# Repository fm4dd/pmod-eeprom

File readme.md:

## PMOD-EEPROM

### Description

This I2C PMOD provides a 1 Mbit serial EEPROM, using the M24M01 circuit by STMicroelectronics. DIP switches enable I2C pull-up resistors if needed, and change the EEPROM's I2C device address. Up to four modules can be chained for a total capacity of 4 Mbit (512 KBytes). Three Testpoints can be fitted for I2C bus troubleshooting. The PMOD has designs for Type-6 (I2C single row), and for the new Type-6A (I2C extended double row). The picture shows the Type-6A variant (engineering sample).

http://fpga.fm4dd.com/

### Schematic
This is the schema for the PMOD I2C Type-6 (single row) connector variant:

The current EEPROM desin is pulling the "write-protect" pin high for "read-write" operation. A design update may implement a solder pad for setting the EEPROM 'read-only' after programming.

### Hardware Release

|Type     | Version | Gerber | Schema |
|---------|---------|--------|--------|
|Type-6   |1.1      |[EEPROM PMOD Type-6 Gerber V1.1](release/t6-v11/20210917-eeprom-t6-gerber-v11.zip) | [20210917-eeprom-t6-schema-v11.pdf](release/t6-v11/20210917-eeprom-t6-schema-v11.pdf)
|Type-6A  |1.1      |[EEPROM PMOD Type-6A Gerber V1.1](release/t6a-v11/20210814-eeprom-t6a-gerber-v11.zip) | [20210814-eeprom-t6a-schema-v11.pdff](release/t6a-v11/20210814-eeprom-t6a-schema-v11.pdf)

#### Rasperry Pi I2C Discovery

Ensure the I2C bus is enabled, and install prerequisite I2C tools:
```
# sudo apt-get install git i2c-tools
# raspi-config  2 Interface Options  enable I2C
```

Check the IO expander circuit is visible on the I2C bus under address 0x50..0x56, depending on the address set through the DIP switch. Below example address 0x50/51 is set with SW1-1 = off and SW1-2 = off.
```
pi@pi-ms05:~ $ i2cdetect -y 1
     0  1  2  3  4  5  6  7  8  9  a  b  c  d  e  f
00:          -- -- -- -- -- -- -- -- -- -- -- -- --
10: -- -- -- -- -- -- -- -- -- -- -- -- -- -- -- --
20: -- -- -- -- -- -- -- -- -- -- -- -- -- -- -- --
30: -- -- -- -- -- -- -- -- -- -- -- -- -- -- -- --
40: -- -- -- -- -- -- -- -- -- -- -- -- -- -- -- --
50: 50 51 -- -- -- -- -- -- -- -- -- -- -- -- -- --
60: -- -- -- -- -- -- -- -- -- -- -- -- -- -- -- --
70: -- -- -- -- -- -- -- --
```

### Example code

pmod-eeprom code examples for Arduino boards are available in the [example folder](examples/)

On the Raspberry Pi, the PMOD can be easily programmed with the eeprom utility program 'eepflash.sh'. This program writes a manually created byte file (.eep) as content into the I2C eeprom. It can be found as part of the Raspberry Pi foundation 'hats' repository:
```
pi@pi-ms05:~ $ git clone https://github.com/raspberrypi/hats.git
Cloning into 'hats'...
remote: Enumerating objects: 565, done.
remote: Counting objects: 100% (95/95), done.
remote: Compressing objects: 100% (61/61), done.
remote: Total 565 (delta 59), reused 46 (delta 34), pack-reused 470
Receiving objects: 100% (565/565), 306.34 KiB | 936.00 KiB/s, done.
Resolving deltas: 100% (325/325), done.
```

Compile the tools located in the eepromutils subdirectory:
```
pi@pi-ms05:~ $ cd hats/eepromutils/
pi@pi-ms05:~/hats/eepromutils $ make clean; make
rm -f eepmake eepdump
cc -Wall -Wextra eepmake.c -o eepmake
cc -Wall -Wextra eepdump.c -o eepdump
```
Check the tools:
```
pi@pi-ms05:~/hats/eepromutils $ ls -l
total 84
-rwxr-xr-x 1 pi pi 12820 Aug 28 22:38 eepdump
-rw-r--r-- 1 pi pi  8112 Aug 28 22:37 eepdump.c
-rwxr-xr-x 1 pi pi  3906 Aug 28 22:37 eepflash.sh
-rwxr-xr-x 1 pi pi 22232 Aug 28 22:38 eepmake
-rw-r--r-- 1 pi pi 15144 Aug 28 22:37 eepmake.c
-rwxr-xr-x 1 pi pi  3122 Aug 28 22:37 eeprom_settings.txt
-rw-r--r-- 1 pi pi  2395 Aug 28 22:37 eeptypes.h
-rw-r--r-- 1 pi pi   677 Aug 28 22:37 Makefile
-rw-r--r-- 1 pi pi  1836 Aug 28 22:37 README.md
```

Example upload of an .eep file:
```
pi@pi-ms05:~/hats/eepromutils $ sudo ./eepflash.sh -w -f=rpi2pmod.eep -t=24c32 -d=1 -a=50
This will attempt to talk to an eeprom at i2c address 0x50 on bus 1. Make sure there is an eeprom at this address.
This script comes with ABSOLUTELY no warranty. Continue only if you know what you are doing.
Do you wish to continue? (yes/no): yes
Writing...
0+1 records in
0+1 records out
113 bytes copied, 0.728222 s, 0.2 kB/s
Closing EEPROM Device.
Done.
```

PMOD-EEPROM on a PMOD2RPI interface board, running code from the XIAO Cortex M0+ MCU.

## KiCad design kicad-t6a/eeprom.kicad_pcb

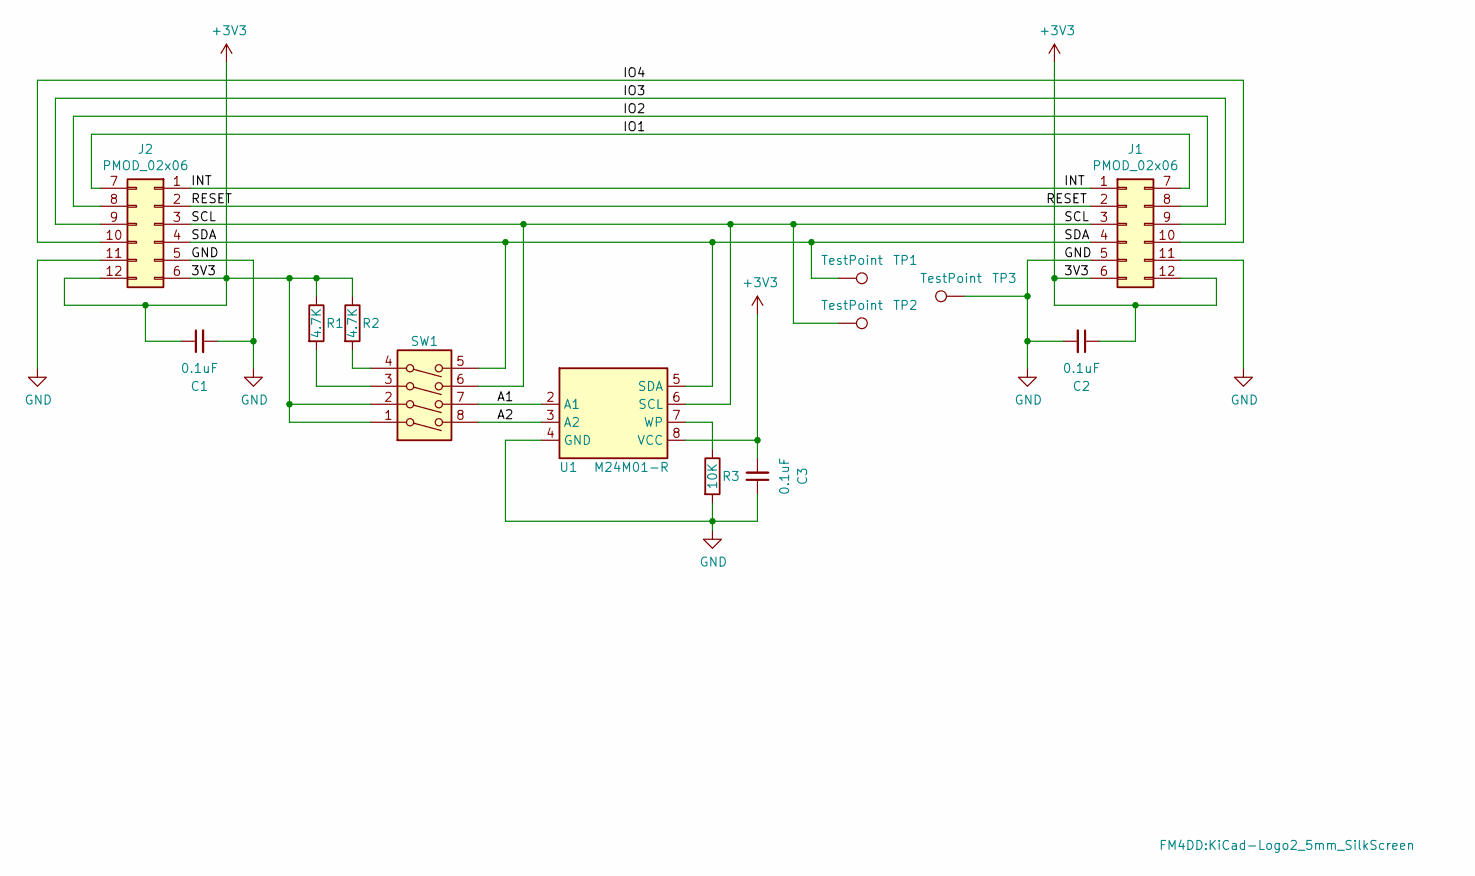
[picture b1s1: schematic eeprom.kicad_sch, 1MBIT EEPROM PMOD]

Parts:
C1, C2, C3: 0.1uF; C_0402_1005Metric
J1: PMOD_02x06; PMODPinSocket_2x06_P2.54mm_Horizontal
J2: PMOD_02x06; PMODHeader_2x06_P2.54mm_Horizontal
L1: Logo_KiCad_5mm; KiCad-Logo2_5mm_SilkScreen
R1, R2: 4.7K; R_0603_1608Metric
R3: 10K; R_0603_1608Metric
SW1: SW_DIP_x04; SW_DIP_SPSTx04_Slide_6.7x11.72mm_W7.62mm_P2.54mm_LowProfile
TP1, TP2, TP3: TestPoint; TestPoint_Keystone_5000-5004_Miniature
U1: M24M01-R; SOIC-8_3.9x4.9mm_P1.27mm

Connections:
+3V3: C1.1, C2.1, C3.2, J1.6, J1.12, J2.6, J2.12, R1.1, R2.1, SW1.1, SW1.2, U1.8 (VCC)
/A1: SW1.7, U1.2 (A1)
/A2: SW1.8, U1.3 (A2)
/INT: J1.1, J2.1
/IO1: J1.7, J2.7
/IO2: J1.8, J2.8
/IO3: J1.9, J2.9
/IO4: J1.10, J2.10
/RESET: J1.2, J2.2
/SCL: J1.3, J2.3, SW1.6, TP2.1, U1.6 (SCL)
/SDA: J1.4, J2.4, SW1.5, TP1.1, U1.5 (SDA)
GND: C1.2, C2.2, C3.1, J1.5, J1.11, J2.5, J2.11, R3.2, TP3.1, U1.4 (GND)
unnamed: R1.2, SW1.3
unnamed: R2.2, SW1.4
unnamed: R3.1, U1.7 (WP)

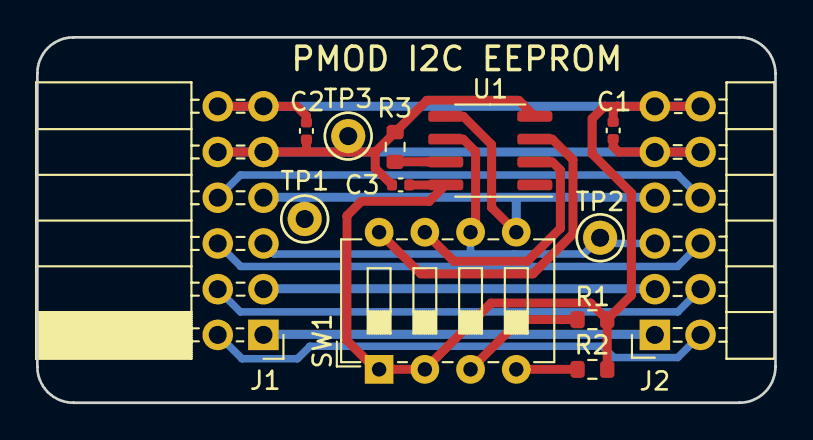
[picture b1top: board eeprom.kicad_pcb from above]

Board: 2 copper layers, 41.0 x 20.3 mm, 15 parts (1 on the bottom side), 15 nets.

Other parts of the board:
Ref**: JLCPCB_Order_Number_Placeholder

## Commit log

2021-10-03 initial check-in
2021-11-03 XIAO example update
2023-11-05 KiCad v7 upgrade, manual workflow trigger

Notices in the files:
kicad-t6/eeprom.kicad_sch:
License: CC-BY-SA 4.0
